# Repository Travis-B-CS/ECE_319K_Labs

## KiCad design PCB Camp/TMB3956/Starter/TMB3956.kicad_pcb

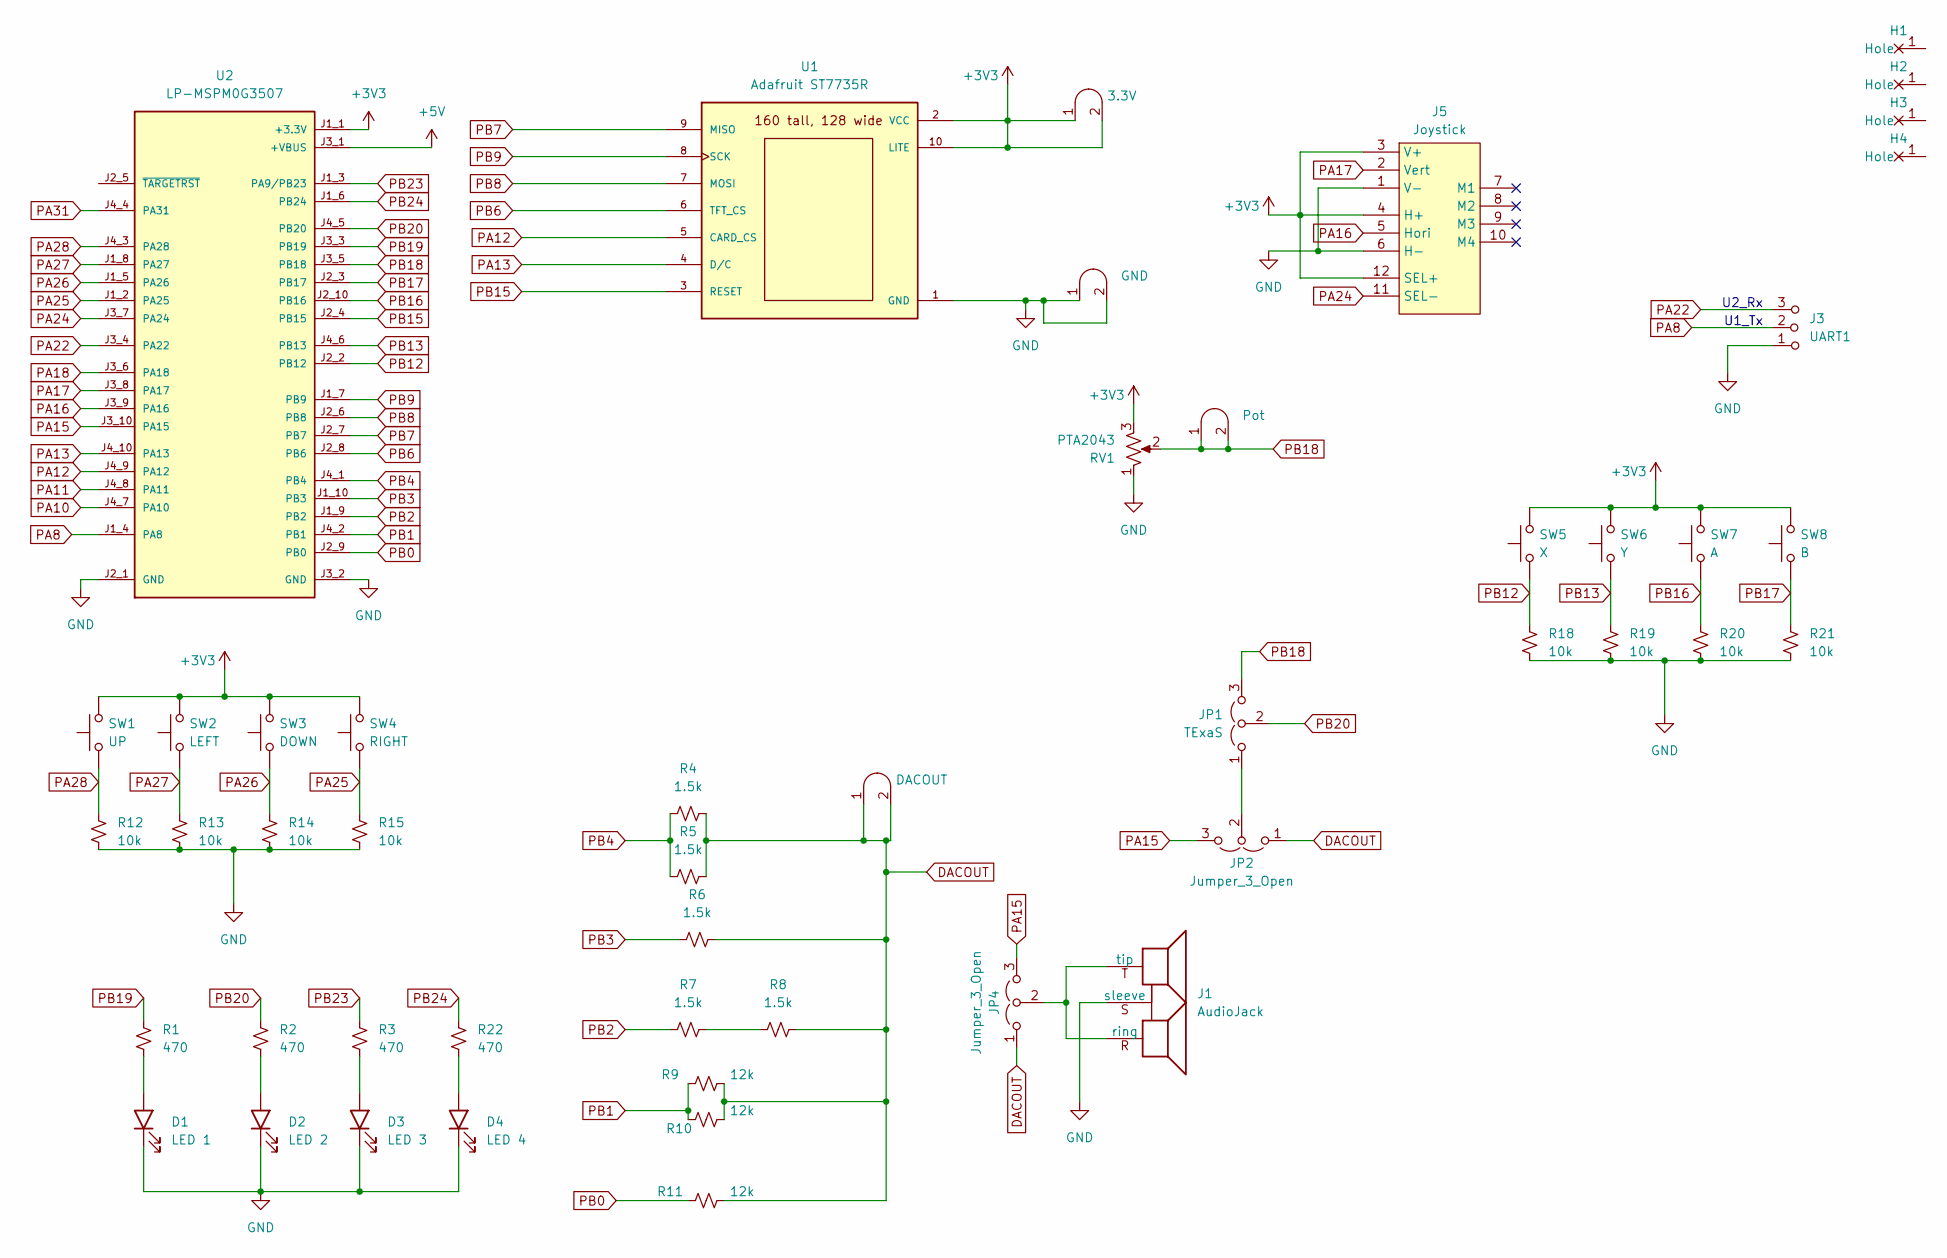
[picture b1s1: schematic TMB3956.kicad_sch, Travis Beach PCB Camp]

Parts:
D1: LED 1; LED_D5.0mm
D2: LED 2; LED_D5.0mm
D3: LED 3; LED_D5.0mm
D4: LED 4; LED_D5.0mm
H1, H2, H3, H4: MountingHole_4_40
J1: AudioJack; Jack_3.5mm_CUI_SJ1-3523N_Horizontal
J3: UART1; PinHeader_1x03_P2.54mm_Vertical
J4: Pot; Testpoint_1x02_P2.54mm
J5: Joystick; SparkfunJoystick
J6: GND; Testpoint_1x02_P2.54mm
J7: DACOUT; Testpoint_1x02_P2.54mm
JP1: TExaS; PinHeader_1x03_P2.54mm_Vertical
JP2, JP4: Jumper_3_Open; PinHeader_1x03_P2.54mm_Vertical
R1, R2, R3, R22: 470; R_Axial_DIN0204_L3.6mm_D1.6mm_P7.62mm_Horizontal
R4, R5, R6, R7, R8: 1.5k; R_Axial_DIN0204_L3.6mm_D1.6mm_P7.62mm_Horizontal
R9, R10, R11: 12k; R_Axial_DIN0204_L3.6mm_D1.6mm_P7.62mm_Horizontal
R12, R13, R14, R15, R18, R19, R20, R21: 10k; R_Axial_DIN0204_L3.6mm_D1.6mm_P7.62mm_Horizontal
RV1: PTA2043; PTA2043pot
SW1: UP; SW_PUSH_6mm
SW2: LEFT; SW_PUSH_6mm
SW3: DOWN; SW_PUSH_6mm
SW4: RIGHT; SW_PUSH_6mm
SW5: X; SW_PUSH_6mm
SW6: Y; SW_PUSH_6mm
SW7: A; SW_PUSH_6mm
SW8: B; SW_PUSH_6mm
TP1: 3.3V; Testpoint_1x02_P2.54mm
U1: Adafruit ST7735R; adafruit_st7735r
U2: LP-MSPM0G3507; ti_LP_MSPM0G3507

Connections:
+3V3: J5.3 (V+), J5.4 (H+), J5.12 (SEL+), RV1.3, SW1.2, SW2.2, SW3.2, SW4.2, SW5.2, SW6.2, SW7.2, SW8.2, TP1.1 (A), TP1.2 (B), U1.2 (VCC), U1.10 (LITE), U2.J1_1 (+3.3V)
+5V: U2.J3_1 (+VBUS)
DACOUT: J7.1 (A), J7.2 (B), JP2.1 (A), JP4.1 (A), R4.1, R5.1, R6.1, R8.1, R9.1, R10.1, R11.1; also elsewhere on the board
GND: D1.1 (K), D2.1 (K), D3.1 (K), D4.1 (K), J1.S (sleeve), J3.1 (A), J5.1 (V-), J5.6 (H-), J6.1 (A), J6.2 (B), R12.2, R13.2, R14.2, R15.2, R18.2, R19.2, R20.2, R21.2, RV1.1, U1.1 (GND), U2.J2_1 (GND), U2.J3_2 (GND); also elsewhere on the board
unnamed: D1.2 (A), R1.2
unnamed: D2.2 (A), R2.2
unnamed: D3.2 (A), R3.2
unnamed: D4.2 (A), R22.2
unnamed: J1.R (ring), J1.T (tip), JP4.2 (C)
unnamed: JP1.1 (A), JP2.2 (C)
unnamed: R7.1, R8.2
PA8: J3.2 (B), U2.J1_4 (PA8)
PA10: U2.J4_7 (PA10)
PA11: U2.J4_8 (PA11)
PA12: U1.5 (CARD_CS), U2.J4_9 (PA12)
PA13: U1.4 (D/C), U2.J4_10 (PA13)
PA15: JP2.3 (B), JP4.3 (B), U2.J3_10 (PA15)
PA16: J5.5 (Hori), U2.J3_9 (PA16)
PA17: J5.2 (Vert), U2.J3_8 (PA17)
PA18: U2.J3_6 (PA18)
PA22: J3.3 (C), U2.J3_4 (PA22)
PA24: J5.11 (SEL-), U2.J3_7 (PA24)
PA25: R15.1, SW4.1, U2.J1_2 (PA25)
PA26: R14.1, SW3.1, U2.J1_5 (PA26)
PA27: R13.1, SW2.1, U2.J1_8 (PA27)
PA28: R12.1, SW1.1, U2.J4_3 (PA28)
PA31: U2.J4_4 (PA31)
PB0: R11.2, U2.J2_9 (PB0)
PB1: R9.2, R10.2, U2.J4_2 (PB1)
PB2: R7.2, U2.J1_9 (PB2)
PB3: R6.2, U2.J1_10 (PB3)
PB4: R4.2, R5.2, U2.J4_1 (PB4)
PB6: U1.6 (TFT_CS), U2.J2_8 (PB6)
PB7: U1.9 (MISO), U2.J2_7 (PB7)
PB8: U1.7 (MOSI), U2.J2_6 (PB8)
PB9: U1.8 (SCK), U2.J1_7 (PB9)
PB12: R18.1, SW5.1, U2.J2_2 (PB12)
PB13: R19.1, SW6.1, U2.J4_6 (PB13)
PB15: U1.3 (RESET), U2.J2_4 (PB15)
PB16: R20.1, SW7.1, U2.J2_10 (PB16)
PB17: R21.1, SW8.1, U2.J2_3 (PB17)
PB18: J4.1 (A), J4.2 (B), JP1.3 (B), RV1.2, U2.J3_5 (PB18); also elsewhere on the board
PB19: R1.1, U2.J3_3 (PB19)
PB20: JP1.2 (C), R2.1, U2.J4_5 (PB20)
PB23: R3.1, U2.J1_3 (PA9/PB23)
PB24: R22.1, U2.J1_6 (PB24)

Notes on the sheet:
U2_Rx
U1_Tx

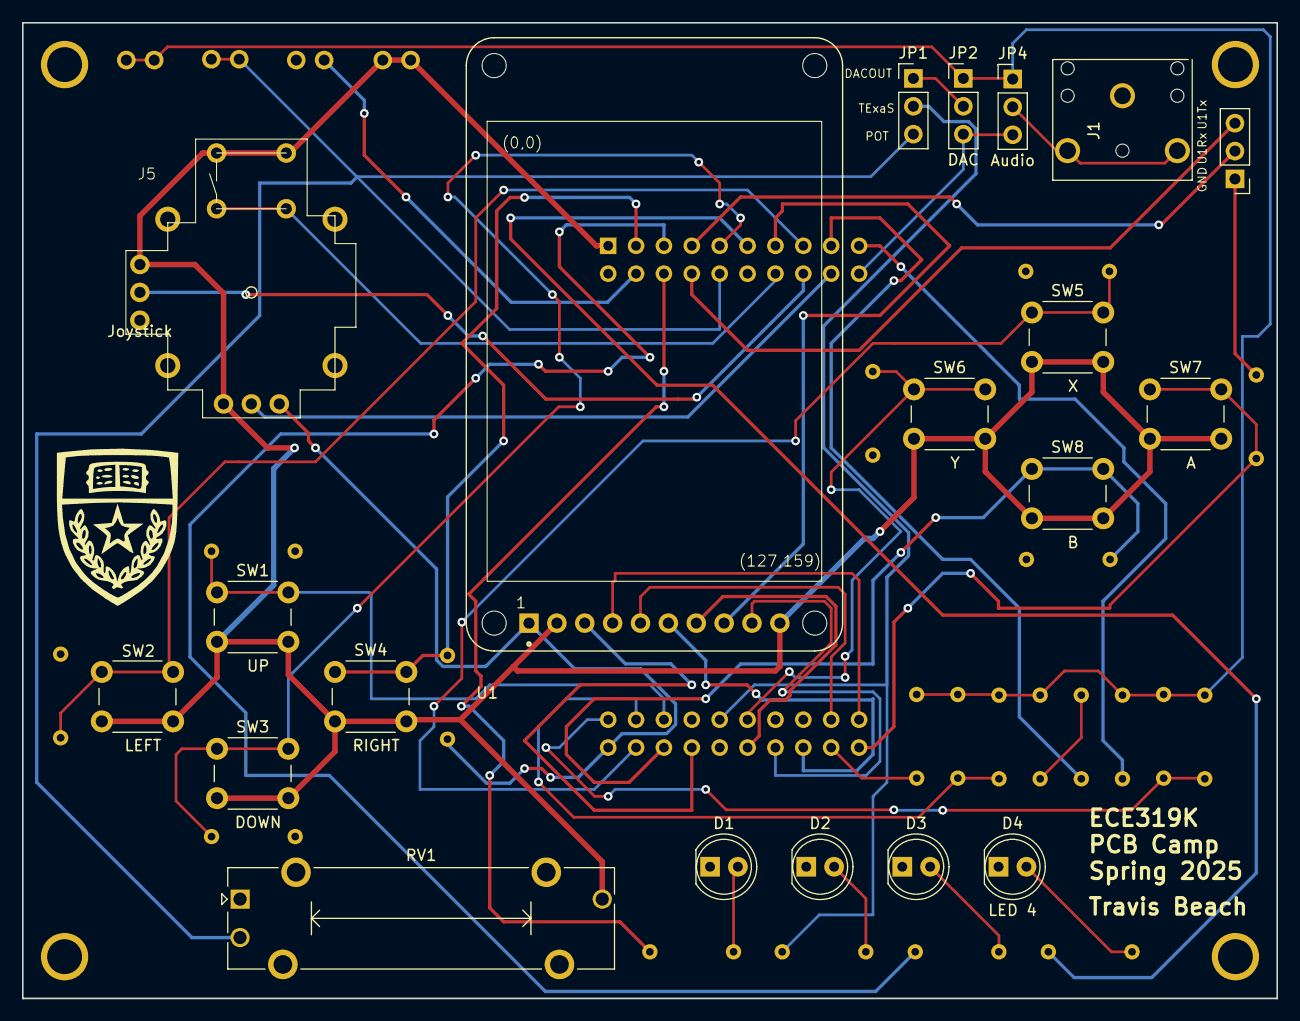
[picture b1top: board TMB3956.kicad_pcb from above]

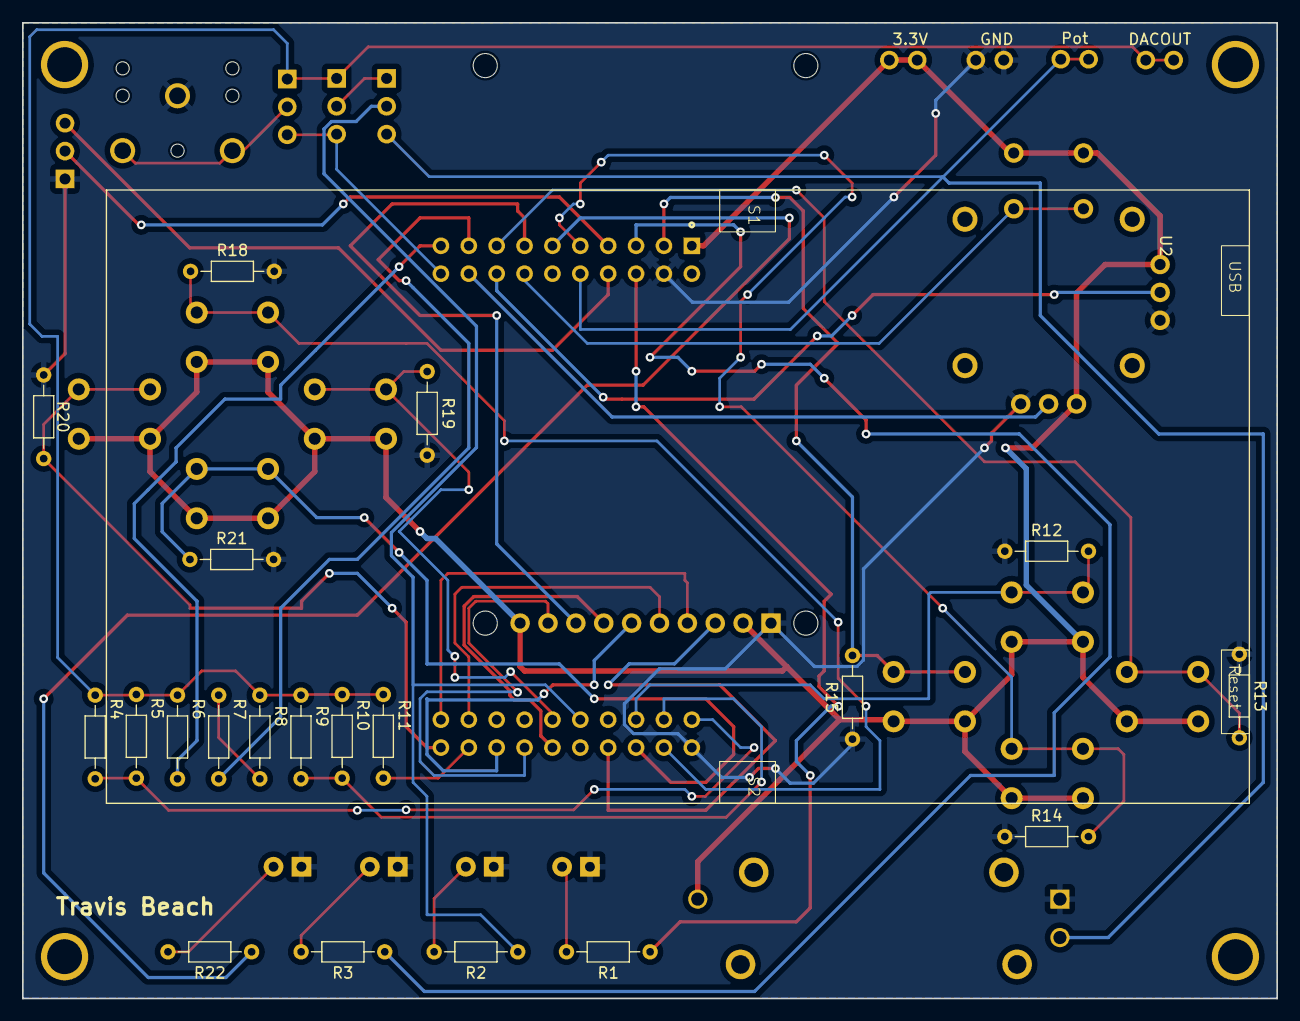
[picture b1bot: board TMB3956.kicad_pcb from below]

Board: 2 copper layers, 114.3 x 88.9 mm, 49 parts (25 on the bottom side), 41 nets.

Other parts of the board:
TP2: GND; Testpoint_1x02_P2.54mm
TP3: Pot; Testpoint_1x02_P2.54mm
TP4: DACOUT; Testpoint_1x02_P2.54mm

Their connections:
DACOUT: TP4.1 (A), TP4.2 (B); also elsewhere on the board
GND: TP2.1 (A), TP2.2 (B); also elsewhere on the board
PB18: TP3.1 (A), TP3.2 (B); also elsewhere on the board

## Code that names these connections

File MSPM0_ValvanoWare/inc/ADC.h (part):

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  <table>
<caption id="ADCpins">ADC pins on the MSPM0G3507</caption>
<tr><th>Pin  <th>ADC channel<th>Sensor
<tr><td>PA27 <td>ADC0 channel 0 <td>J1.8 also MKII light interrupt
<tr><td>PA26 <td>ADC0 channel 1 <td>J1.6 MKII microphone in
<tr><td>PA25 <td>ADC0 channel 2 <td>J1.2 MKII Joystick X
<tr><td>PA24 <td>ADC0 channel 3 <td>J3.27 ***free***
<tr><td>PB25 <td>ADC0 channel 4 <td>J19.7 (insert 0ohm R74, no U3 OPA2365)
<tr><td>PB24 <td>ADC0 channel 5 <td>J1.5 also MKII joystick select button
<tr><td>PB20 <td>ADC0 channel 6 <td>J4.36 ***free***
<tr><td>PA22 <td>ADC0 channel 7 <td>J24 MKII Accelerometer Y

<tr><td>PA15 <td>ADC1 channel 0 <td>J3.30 (also DACout)
<tr><td>PA16 <td>ADC1 channel 1 <td>J3.29 ***free***
<tr><td>PA17 <td>ADC1 channel 2 <td>J3.28 ***free***
<tr><td>PA18 <td>ADC1 channel 3 <td>J3.26 MKII Joystick Y
<tr><td>PB17 <td>ADC1 channel 4 <td>J2.18 ***free***
<tr><td>PB18 <td>ADC1 channel 5 <td>J3.25 MKII Accelerometer Z
<tr><td>PB19 <td>ADC1 channel 6 <td>J3.23 MKII Accelerometer X
<tr><td>PA21 <td>ADC1 channel 7 <td>J17.8 (insert R20, remove R3)

</table>
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 <table>
<caption id="ADCpins2">ADC pins on the MSPM0G3507</caption>
<tr><th>Pin  <th>ADC channel<th>Sensor
<tr><td>PA27 <td>ADC0 channel 0 <td>J1.8 also MKII light interrupt
<tr><td>PA26 <td>ADC0 channel 1 <td>J1.6 MKII microphone in
<tr><td>PA25 <td>ADC0 channel 2 <td>J1.2 MKII Joystick X
<tr><td>PA24 <td>ADC0 channel 3 <td>J3.27 ***free***
<tr><td>PB25 <td>ADC0 channel 4 <td>J19.7 (insert 0ohm R74, no U3 OPA2365)
<tr><td>PB24 <td>ADC0 channel 5 <td>J1.5 also MKII joystick select button
<tr><td>PB20 <td>ADC0 channel 6 <td>J4.36 ***free***
<tr><td>PA22 <td>ADC0 channel 7 <td>J24 MKII Accelerometer Y

<tr><td>PA15 <td>ADC1 channel 0 <td>J3.30 (also DACout)
<tr><td>PA16 <td>ADC1 channel 1 <td>J3.29 ***free***
<tr><td>PA17 <td>ADC1 channel 2 <td>J3.28 ***free***
<tr><td>PA18 <td>ADC1 channel 3 <td>J3.26 MKII Joystick Y
<tr><td>PB17 <td>ADC1 channel 4 <td>J2.18 ***free***
<tr><td>PB18 <td>ADC1 channel 5 <td>J3.25 MKII Accelerometer Z
<tr><td>PB19 <td>ADC1 channel 6 <td>J3.23 MKII Accelerometer X
<tr><td>PA21 <td>ADC1 channel 7 <td>J17.8 (insert R20, remove R3)

</table>
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 * measurements when the associated function is called.
 * One channel is to be measured<br>
 *  Pin  channel<br>
 *  PA27 0 <br>
 *  PA26 1 <br>
 *  PA25 2 <br>
 *  PA24 3 <br>
 *  PB25 4 <br>
 *  PB24 5 <br>
 *  PB20 6 <br>
 *  PA22 7 
 * @param channel is the 0 to 7
 * @param reference is ADCVREF_INT, ADCVREF_EXT, ADCVREF_VDDA
 * @return none 
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 * measurements when the associated function is called.
 * One channel is to be measured<br>
 *  Pin  channel<br>
 *  PA15 0 <br>
 *  PA16 1 <br>
 *  PA17 2 <br>
 *  PA18 3 <br>
 *  PB17 4 <br>
 *  PB18 5 <br>
 *  PB19 6 <br>
 *  PA21 7 
 * @param channel is the 0 to 7
 * @param reference is ADCVREF_INT, ADCVREF_EXT, ADCVREF_VDDA
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  <table>
<caption id="ADCpins3">ADC pins on the MSPM0G3507</caption>
<tr><th>Pin  <th>ADC channel
<tr><td>PA27 <td>ADC0 channel 0 
<tr><td>PA26 <td>ADC0 channel 1 
<tr><td>PA25 <td>ADC0 channel 2 
<tr><td>PA24 <td>ADC0 channel 3 
<tr><td>PB25 <td>ADC0 channel 4
<tr><td>PB24 <td>ADC0 channel 5 
<tr><td>PB20 <td>ADC0 channel 6 
<tr><td>PA22 <td>ADC0 channel 7 

<tr><td>PA15 <td>ADC1 channel 0 
<tr><td>PA16 <td>ADC1 channel 1 
<tr><td>PA17 <td>ADC1 channel 2 
<tr><td>PA18 <td>ADC1 channel 3 
<tr><td>PB17 <td>ADC1 channel 4 
<tr><td>PB18 <td>ADC1 channel 5 
<tr><td>PB19 <td>ADC1 channel 6 
<tr><td>PA21 <td>ADC1 channel 7 
</table>
 * @param adc12 is ADC0 or ADC1
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
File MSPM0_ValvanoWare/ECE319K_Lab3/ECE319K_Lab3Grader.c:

/* ECE319K_Lab3Grader.c
 * Jonathan Valvano
 * December 9, 2024
 * Derived from uart_rw_multibyte_fifo_poll_LP_MSPM0G3507_nortos_ticlang
 */
/*
 Copyright 2025 by Jonathan W. Valvano, valvano@mail.utexas.edu
    You may use, edit, run or distribute this file
    as long as the above copyright notice remains
 THIS SOFTWARE IS PROVIDED "AS IS".  NO WARRANTIES, WHETHER EXPRESS, IMPLIED
 OR STATUTORY, INCLUDING, BUT NOT LIMITED TO, IMPLIED WARRANTIES OF
 MERCHANTABILITY AND FITNESS FOR A PARTICULAR PURPOSE APPLY TO THIS SOFTWARE.
 VALVANO SHALL NOT, IN ANY CIRCUMSTANCES, BE LIABLE FOR SPECIAL, INCIDENTAL,
 OR CONSEQUENTIAL DAMAGES, FOR ANY REASON WHATSOEVER.
 For more information about my classes, my research, and my books, see
 http://users.ece.utexas.edu/~valvano/
 */
#include <ti/devices/msp/msp.h>
#include "../inc/LaunchPad.h"
#include "../inc/Clock.h"
#include "../inc/UART.h"
#include "../inc/Timer.h"
#include "../inc/Dump.h"
#include <stdio.h>
#include <string.h>

// PA10 is UART0 Tx    index 20 in IOMUX PINCM table
// PA11 is UART0 Rx    index 21 in IOMUX PINCM table
// Insert jumper J25: Connects PA10 to XDS_UART
// Insert jumper J26: Connects PA11 to XDS_UART
// Switch input PB2 PB1 or PB0
// LED output PB18 PB17 or PB16
// logic analyzer pins PB18 PB17 PB16 PB2 PB1 PB0
// analog scope pin PB20, channel 6
uint32_t Score;


extern const char Lab3EID[20]; // student's EID
extern uint32_t DataBuffer[50];
extern uint32_t TimeBuffer[50];

void Lab3Grader(void){
  uint32_t elapsed,start,end,offset,result,ok;
  uint32_t Period0,Period1,Period2,Period7,Period8;
  Clock_Init80MHz(0);
  LaunchPad_Init();
  UART_Init();
  SysTick->CTRL = 0;           // 1) disable SysTick during setup
  SysTick->LOAD = 0xFFFFFF;    // 2) max
  SysTick->VAL = 0;            // 3) any write to current clears it
  SysTick->CTRL = 0x00000005;  // 4) enable SysTick with core clock
  Score = 0;
  if(strcmp(Lab3EID,"ZZZ123")==0){
    UART_OutString("Please your EID in ECE319K_Lab3main.c");
    while(1);
  }
  // grader basically repeats the manual testing
  Score = 0;
  UART_OutString("\n\rLab 3, Spring 2025, Grader. \n\r");
  UART_OutString("EID= "); UART_OutString((char*)Lab3EID); UART_OutString("\n\rStep 1) ");
  Debug_Init(); // calls your Lab 3 function
  Debug_Dump(2);
  Clock_Delay(80000000); // 1s
  Debug_Dump(3);
  uint32_t time = TimeBuffer[0]-TimeBuffer[1]; // should be about 80000000
  uint32_t data0 = DataBuffer[0];
  uint32_t data1 = DataBuffer[1];
  if(data0 == 2) Score += 2;
  if(data1 == 3) Score += 2;
  if((time > 75000000)&&(time < 85000000)) Score += 1;
  UART_OutString("Score= "); UART_OutUDec(Score); UART_OutString("\n\rStep 2) ");
  Debug_Init(); // calls your Lab 3 function
  for(int i = 0; i<2; i++){ // only 16 points
    for(int j=0; j<8; j++){
      Debug_Dump(j);
      Clock_Delay(80000); // 1ms
    }
  }
  ok = 1;
  for(int i=0; i<16;i++){
    if(DataBuffer[i] != (i&0x07)){
      ok = 0;
    }
  }
  if(ok){
    Score += 5;
  }
  UART_OutString("Score= "); UART_OutUDec(Score); UART_OutString("\n\rStep 3) ");
  Debug_Init(); // calls your Lab 3 function
  for(int i = 0; i<10; i++){ // called 80 times to fill and go beyond
    for(int j=0; j<8; j++){
      Debug_Dump(j);
      Clock_Delay(40000); // 0.5ms
    }
  }
  ok = 1;
  for(int i=0; i<50;i++){
    if(DataBuffer[i] != (i&0x07)){
      ok = 0;
    }
  }
  if(ok){
    Period0 = Debug_Period(1); // should be about 80000 (1ms)
    if((Period0 > 75000)&&(Period0 < 85000)) Score += 2;
    Period1 = Debug_Period(2); // should be about 160000 (2ms)
    if((Period1 > 155000)&&(Period1 < 165000)) Score += 2;
    Period2 = Debug_Period(4); // should be about 320000 (4ms)
    if((Period2 > 315000)&&(Period2 < 325000)) Score += 2;
    Period7 = Debug_Period(7); // should be about 320000 (4ms)
    if((Period7 > 315000)&&(Period7 < 325000)) Score += 2;
    Period8 = Debug_Period(8); // should be exactly 0 (no edges)
    if(Period8  == 0) Score += 2;
  }
  UART_OutString("Score= "); UART_OutUDec(Score); UART_OutString("\n\rStep 4) ");
  start = SysTick->VAL;
  end = SysTick->VAL;
  offset = (start-end)&0xFFFFFF; // calibration
  start = SysTick->VAL;
  result = Debug_Dump(1);
  end = SysTick->VAL;
  elapsed = (start-end-offset)&0xFFFFFF; // units of 12.5ns
  if(elapsed < 300){
    Score +=5;
  }
  else{
   UART_OutString("Too slow, execution time= "); UART_OutUDec(elapsed); UART_OutString(" cycles, ");
  }
  UART_OutString("Score= "); UART_OutUDec(Score); UART_OutString(" out of 25\n\rDone\n\r");

}

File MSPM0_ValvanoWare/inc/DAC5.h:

/**
 * @file      DAC5.h
 * @brief     5-bit binary-weighted DAC
 * @details   Lab 5. Digital Piano using a Digital to Analog Converter<br>
 * For more information see<br> https://docs.google.com/document/d/1DVmHjqsx24FvLp4x8KKyr5UmDeDlBlfeQPsVvKFQF_k/edit<br>
 * @version   ECE319K Spring 2025
 * @author    Travis and Jonathan
 * @copyright Lab solution, do not post,
 * @warning   AS-IS
 * @note      For more information see  http://users.ece.utexas.edu/~valvano/
 * @date      Feburary 28, 2025
  <table>
<caption id="Lab5pins">Pins on the 5-bit DAC</caption>
<tr><th>Pin <th>GPIO<th>Hardware
<tr><td>PB4 <td>output<td>bit 4 (most significant)
<tr><td>PB3 <td>output<td>bit 3
<tr><td>PB2 <td>output<td>bit 2
<tr><td>PB1 <td>output<td>bit 1
<tr><td>PB0 <td>output<td>bit 0 (least significant)
</table>
  ******************************************************************************/
#ifndef __DAC5_H__
#define __DAC5_H__

/**
 * Initialize 5-bit DAC
 *    - PB4 output MSBit
 *    - PB3 output
 *    - PB2 output
 *    - PB1 output
 *    - PB0 output LSBit
 * @param none
 * @return none
 * @brief  Initialize DAC
 * @note LaunchPad_Init has been called; this program should not reset Port B
 */
void DAC5_Init(void);

/**
 * Output to 5-bit DAC
 * @param data is 5-bit value to output, 0 to 31
 * @return none
 * @brief  Output to DAC5
 * @note this solution must be friendly
 */
void DAC5_Out(uint32_t data);

#endif // __DAC5_H__

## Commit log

2026-01-16 Uploaded ECE 319K Labs
2026-01-16 Added Lab Reports
2026-01-30 Used Calibration Excel for ECE 445L Lab

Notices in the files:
MSPM0_ValvanoWare/inc/ADC.h:
@copyright Copyright 2025 by Jonathan W. Valvano, valvano@mail.utexas.edu,
@warning AS-IS
